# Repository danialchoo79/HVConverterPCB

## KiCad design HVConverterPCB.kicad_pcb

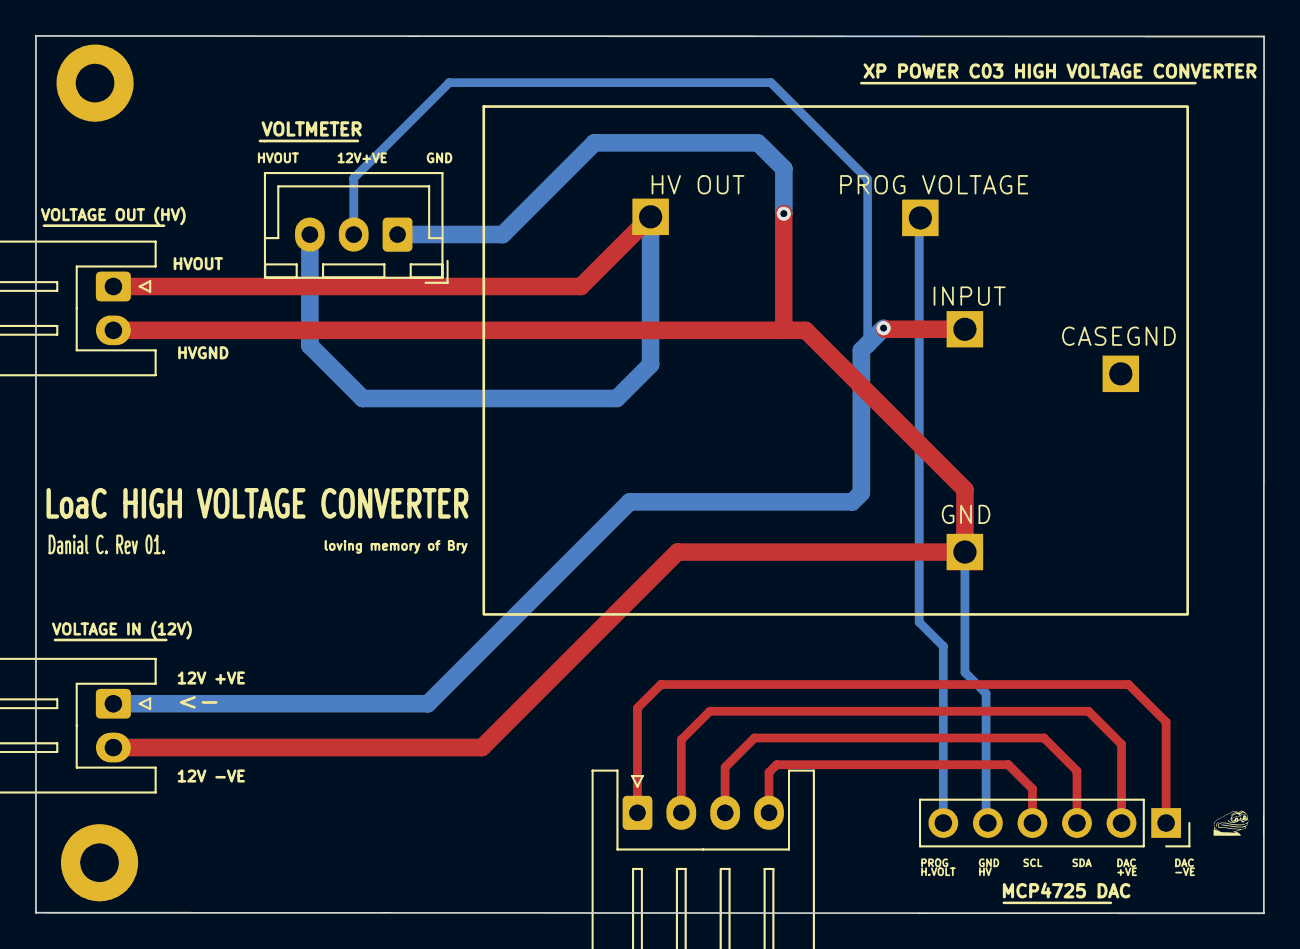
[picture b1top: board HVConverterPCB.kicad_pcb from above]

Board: 2 copper layers, 70.0 x 50.0 mm, 8 parts (0 on the bottom side), 8 nets.

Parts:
H1, H2: MountingHole; MountingHole_2.2mm_M2_Pad
J3: VOUT; JST_XH_S2B-XH-A_1x02_P2.50mm_Horizontal
J4: JST_CONN_VIN; JST_XH_S2B-XH-A_1x02_P2.50mm_Horizontal
J5: JST_CONN_DAC; JST_XH_S4B-XH-A_1x04_P2.50mm_Horizontal
J6: Conn_01x03; JST_XH_B3B-XH-A_1x03_P2.50mm_Vertical
J7: MCP4725_DUPONT_CONN; PinSocket_1x06_P2.54mm_Vertical
U1: XPPower_C03

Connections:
DAC_OUT: J3.1, J6.3, U1.5 (DAC_OUT)
GNDPWR: J3.2, J4.2, J6.1, J7.5, U1.2 (-VOUT)
GND_DAC: J5.1, J7.1
SCL_DAC: J5.4, J7.4
SDA_DAC: J5.3, J7.3
VCC: J7.6, U1.3 (+VIN)
VCC_DAC: J5.2, J7.2
VPP: J4.1, J6.2, U1.1 (+VOUT)

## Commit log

2025-03-19 Removed Via Stitching, Copper Pours
2025-03-19 Added more silkscreens
